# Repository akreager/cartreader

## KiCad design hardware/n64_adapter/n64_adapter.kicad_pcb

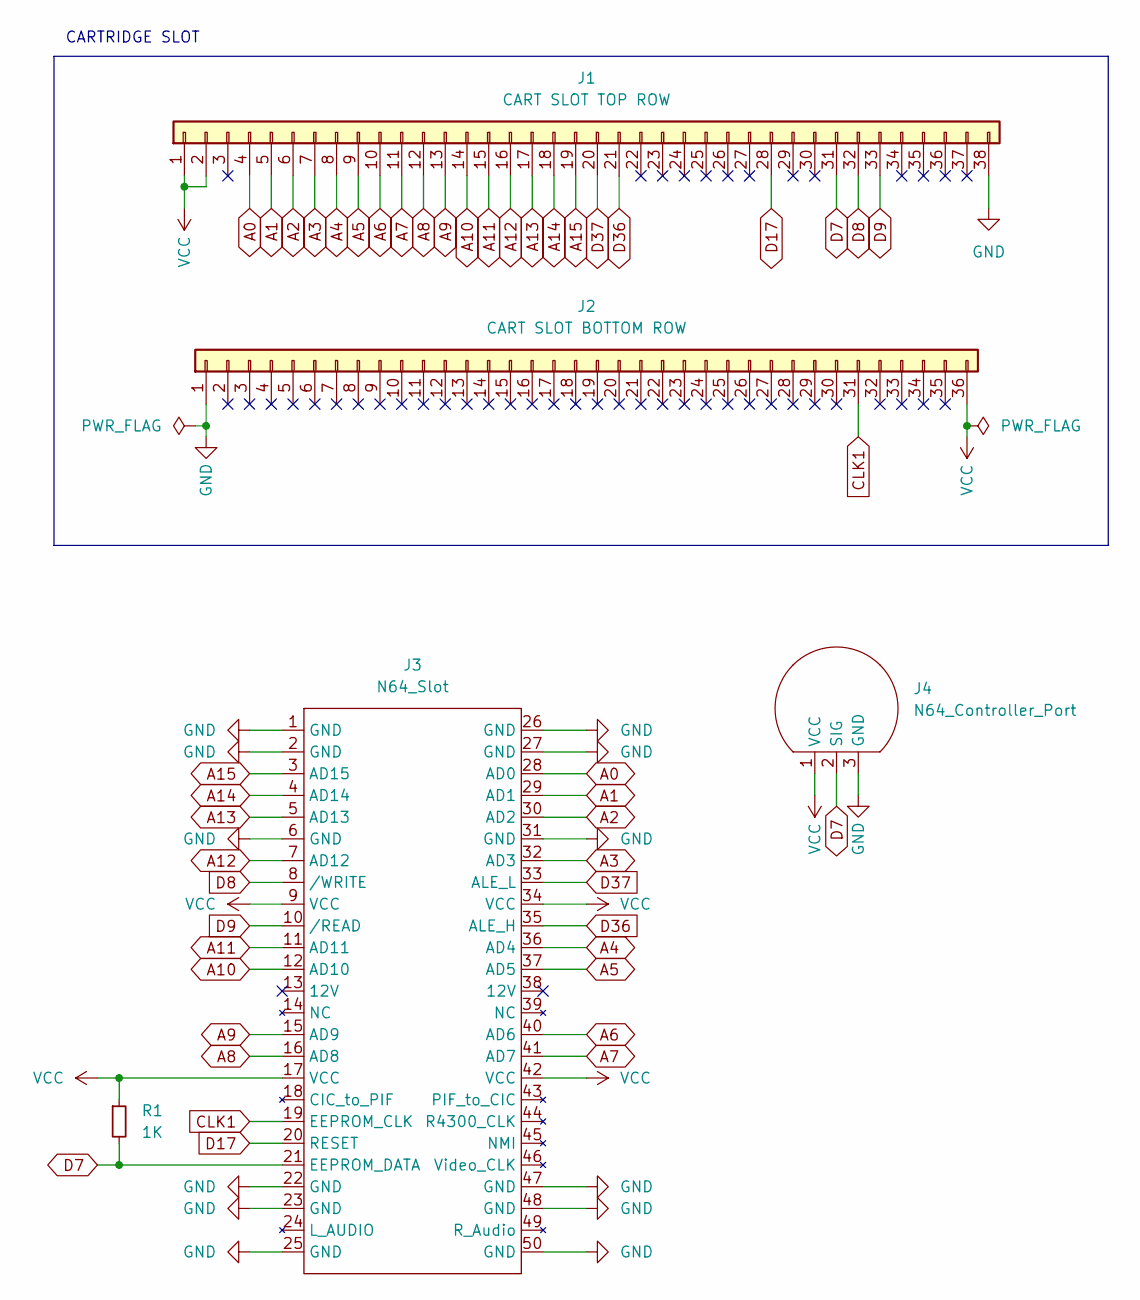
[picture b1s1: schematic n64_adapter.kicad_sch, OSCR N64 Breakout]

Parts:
J1: CART SLOT TOP ROW; PinHeader_1x38_P2.54mm_Vertical
J2: CART SLOT BOTTOM ROW; PinHeader_1x36_P2.54mm_Vertical
J3: N64_Slot; N64 Slot
J4: N64_Controller_Port; N64_CONTROLLER_PORT
R1: 1K; R_Axial_DIN0207_L6.3mm_D2.5mm_P10.16mm_Horizontal

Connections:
A0: J1.4, J3.28 (AD0)
A1: J1.5, J3.29 (AD1)
A2: J1.6, J3.30 (AD2)
A3: J1.7, J3.32 (AD3)
A4: J1.8, J3.36 (AD4)
A5: J1.9, J3.37 (AD5)
A6: J1.10, J3.40 (AD6)
A7: J1.11, J3.41 (AD7)
A8: J1.12, J3.16 (AD8)
A9: J1.13, J3.15 (AD9)
A10: J1.14, J3.12 (AD10)
A11: J1.15, J3.11 (AD11)
A12: J1.16, J3.7 (AD12)
A13: J1.17, J3.5 (AD13)
A14: J1.18, J3.4 (AD14)
A15: J1.19, J3.3 (AD15)
CLK1: J2.31, J3.19 (EEPROM_CLK)
D7: J1.31, J3.21 (EEPROM_DATA), J4.2 (SIG), R1.2
D8: J1.32, J3.8 (/WRITE)
D9: J1.33, J3.10 (/READ)
D17: J1.28, J3.20 (RESET)
D36: J1.21, J3.35 (ALE_H)
D37: J1.20, J3.33 (ALE_L)
GND: J1.38, J2.1, J3.1 (GND), J3.2 (GND), J3.6 (GND), J3.22 (GND), J3.23 (GND), J3.25 (GND), J3.26 (GND), J3.27 (GND), J3.31 (GND), J3.47 (GND), J3.48 (GND), J3.50 (GND), J4.3 (GND)
VCC: J1.1, J1.2, J2.36, J3.9 (VCC), J3.17 (VCC), J3.34 (VCC), J3.42 (VCC), J4.1 (VCC), R1.1

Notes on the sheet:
CARTRIDGE SLOT

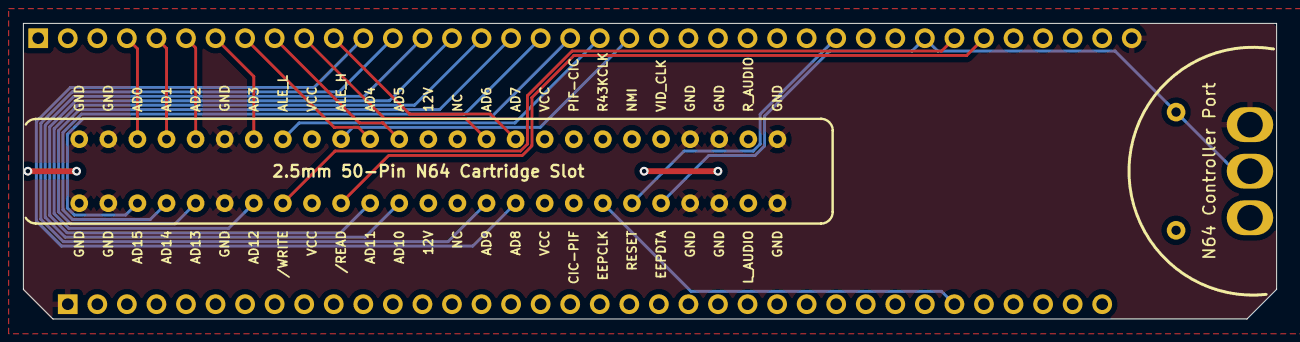
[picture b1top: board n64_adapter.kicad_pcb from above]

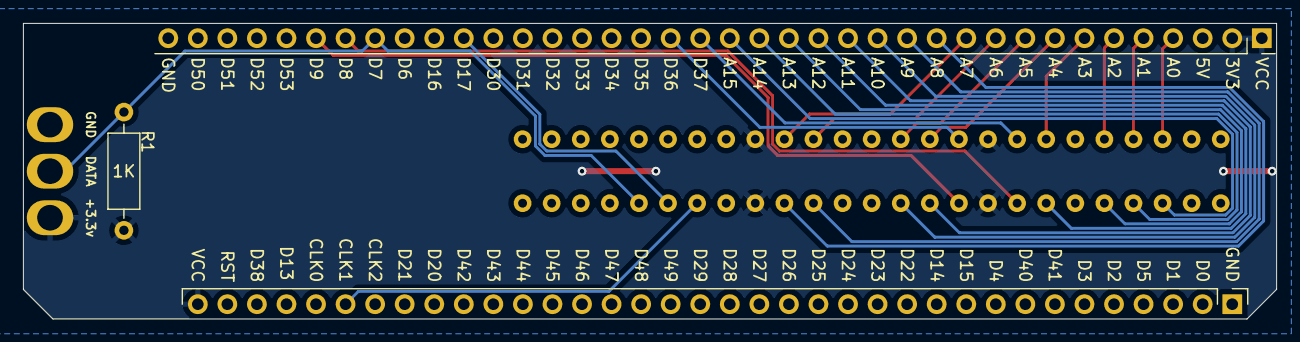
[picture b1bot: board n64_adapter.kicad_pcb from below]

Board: 2 copper layers, 107.7 x 25.4 mm, 5 parts (3 on the bottom side), 25 nets.

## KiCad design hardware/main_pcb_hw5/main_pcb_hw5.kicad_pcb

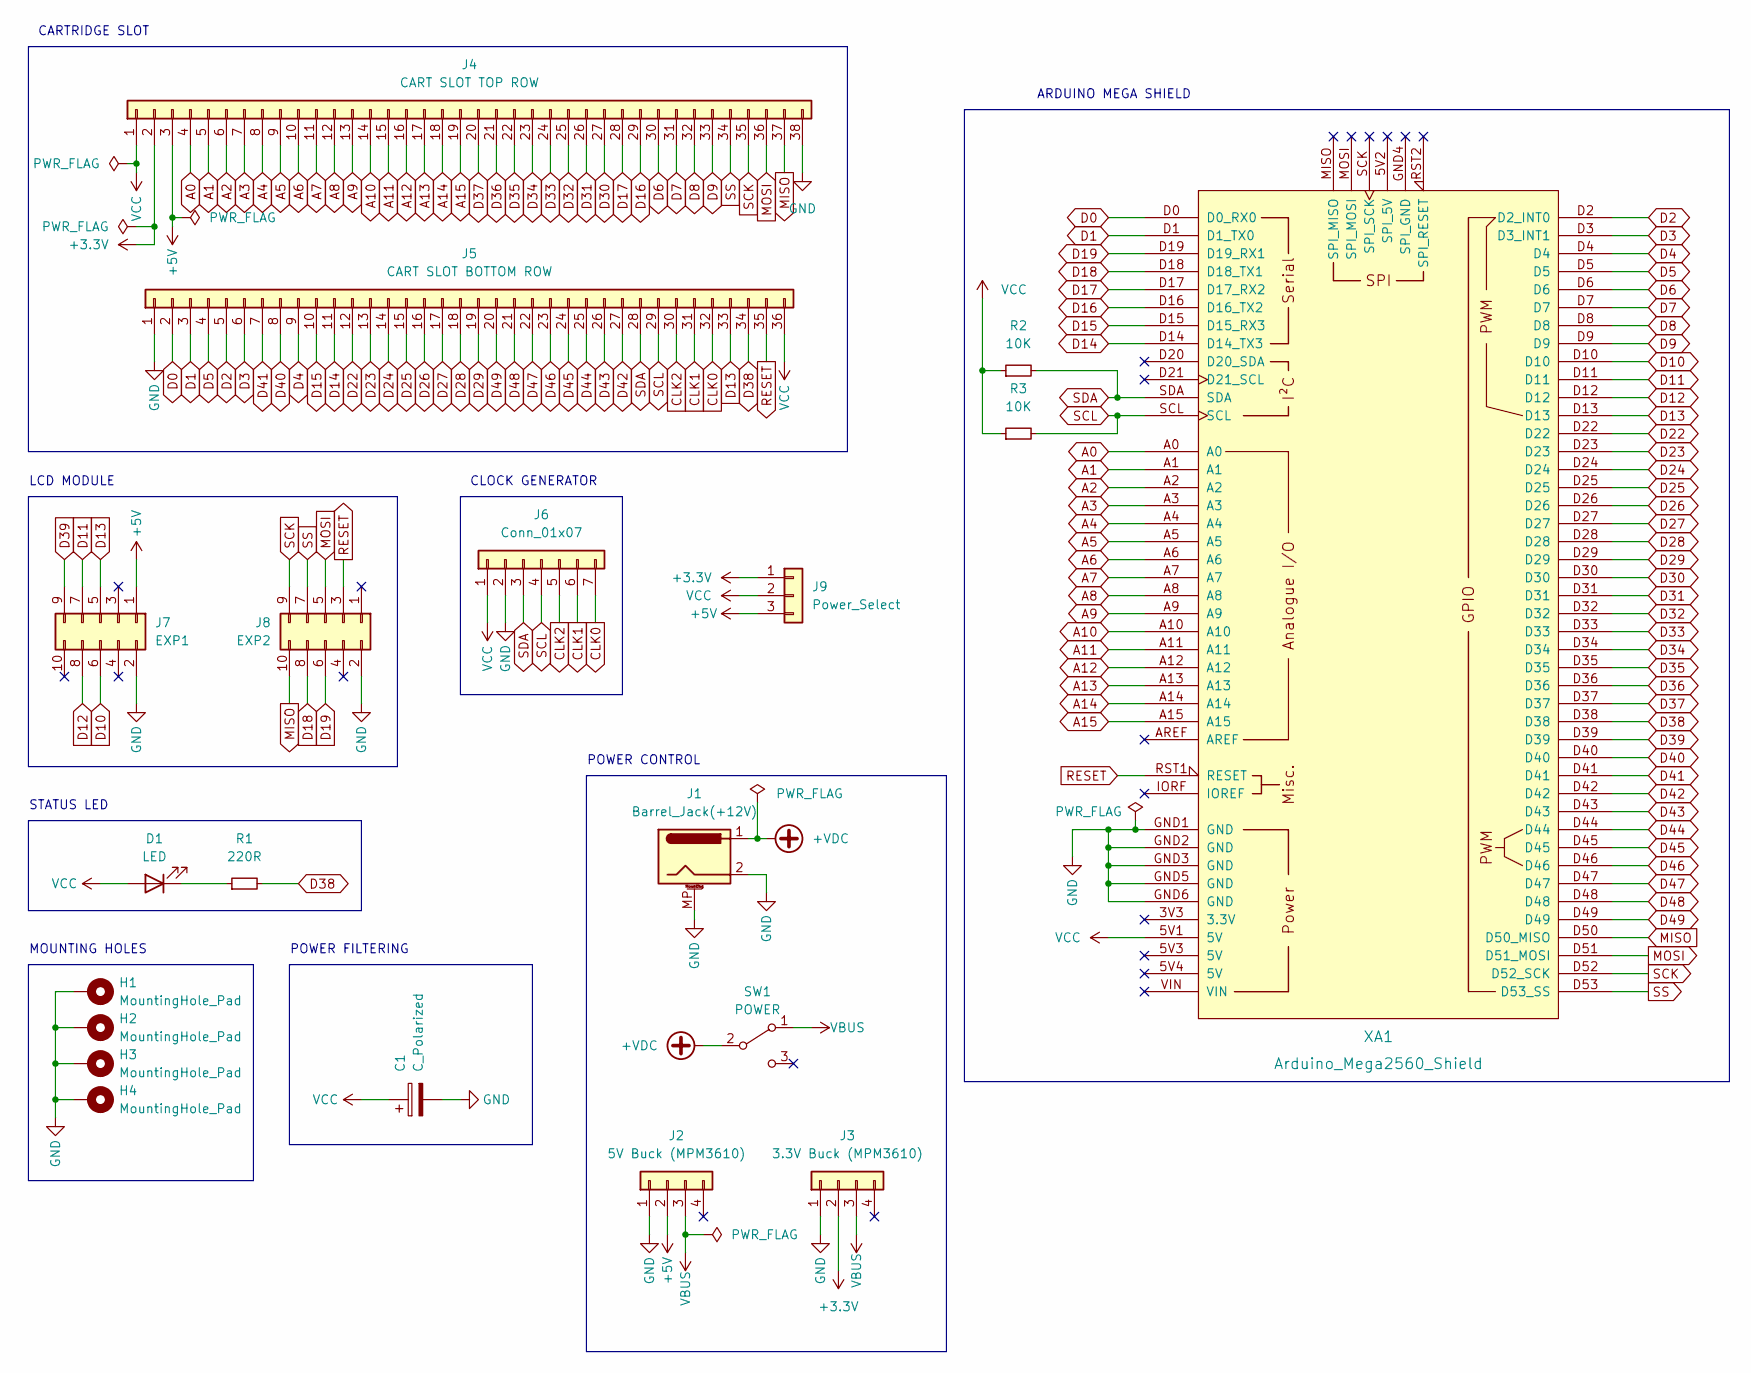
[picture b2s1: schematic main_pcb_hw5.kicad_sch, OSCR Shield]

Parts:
C1: C_Polarized; CP_Radial_D8.0mm_P3.50mm
D1: LED; LED_D3.0mm
H1, H2, H3, H4: MountingHole_Pad; MountingHole_3.2mm_M3_Pad
J1: Barrel_Jack(+12V); BarrelJack_Horizontal
J2: 5V Buck (MPM3610); PinHeader_1x04_P2.54mm_Vertical
J3: 3.3V Buck (MPM3610); PinHeader_1x04_P2.54mm_Vertical
J4: CART SLOT TOP ROW; PinSocket_1x38_P2.54mm_Vertical
J5: CART SLOT BOTTOM ROW; PinSocket_1x36_P2.54mm_Vertical
J6: Conn_01x07; PinSocket_1x07_P2.54mm_Vertical
J7: EXP1; IDC-Header_2x05_P2.54mm_Vertical
J8: EXP2; IDC-Header_2x05_P2.54mm_Vertical
J9: Power_Select; PinHeader_1x03_P2.54mm_Vertical
R1: 220R; R_Axial_DIN0207_L6.3mm_D2.5mm_P7.62mm_Horizontal
R2, R3: 10K; R_Axial_DIN0207_L6.3mm_D2.5mm_P7.62mm_Horizontal
SW1: POWER; SW_CuK_OS102011MA1QN1_SPDT_Angled
XA1: Arduino_Mega2560_Shield

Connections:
+3.3V: J3.2, J4.2, J9.1
+5V: J2.2, J4.3, J7.1, J9.3
+VDC: J1.1, SW1.2 (B)
A0: J4.4, XA1.A0
A1: J4.5, XA1.A1
A2: J4.6, XA1.A2
A3: J4.7, XA1.A3
A4: J4.8, XA1.A4
A5: J4.9, XA1.A5
A6: J4.10, XA1.A6
A7: J4.11, XA1.A7
A8: J4.12, XA1.A8
A9: J4.13, XA1.A9
A10: J4.14, XA1.A10
A11: J4.15, XA1.A11
A12: J4.16, XA1.A12
A13: J4.17, XA1.A13
A14: J4.18, XA1.A14
A15: J4.19, XA1.A15
CLK0: J5.32, J6.7
CLK1: J5.31, J6.6
CLK2: J5.30, J6.5
D0: J5.2, XA1.D0 (D0_RX0)
D1: J5.3, XA1.D1 (D1_TX0)
D2: J5.5, XA1.D2 (D2_INT0)
D3: J5.6, XA1.D3 (D3_INT1)
D4: J5.9, XA1.D4
D5: J5.4, XA1.D5
D6: J4.30, XA1.D6
D7: J4.31, XA1.D7
D8: J4.32, XA1.D8
D9: J4.33, XA1.D9
D10: J7.6, XA1.D10
D11: J7.7, XA1.D11
D12: J7.8, XA1.D12
D13: J5.33, J7.5, XA1.D13
D14: J5.11, XA1.D14 (D14_TX3)
D15: J5.10, XA1.D15 (D15_RX3)
D16: J4.29, XA1.D16 (D16_TX2)
D17: J4.28, XA1.D17 (D17_RX2)
D18: J8.8, XA1.D18 (D18_TX1)
D19: J8.6, XA1.D19 (D19_RX1)
D22: J5.12, XA1.D22
D23: J5.13, XA1.D23
D24: J5.14, XA1.D24
D25: J5.15, XA1.D25
D26: J5.16, XA1.D26
D27: J5.17, XA1.D27
D28: J5.18, XA1.D28
D29: J5.19, XA1.D29
D30: J4.27, XA1.D30
D31: J4.26, XA1.D31
D32: J4.25, XA1.D32
D33: J4.24, XA1.D33
D34: J4.23, XA1.D34
D35: J4.22, XA1.D35
D36: J4.21, XA1.D36
D37: J4.20, XA1.D37
D38: J5.34, R1.2, XA1.D38
D39: J7.9, XA1.D39
D40: J5.8, XA1.D40
D41: J5.7, XA1.D41
D42: J5.27, XA1.D42
D43: J5.26, XA1.D43
D44: J5.25, XA1.D44
D45: J5.24, XA1.D45
D46: J5.23, XA1.D46
D47: J5.22, XA1.D47
D48: J5.21, XA1.D48
D49: J5.20, XA1.D49
GND: C1.2, H1.1, H2.1, H3.1, H4.1, J1.2, J1.MP (MountPin), J2.1, J3.1, J4.38, J5.1, J6.2, J7.2, J8.2, XA1.GND1 (GND), XA1.GND2 (GND), XA1.GND3 (GND), XA1.GND5 (GND), XA1.GND6 (GND)
MISO: J4.37, J8.10, XA1.D50 (D50_MISO)
MOSI: J4.36, J8.5, XA1.D51 (D51_MOSI)
unnamed: D1.1 (K), R1.1
RESET: J5.35, J8.3, XA1.RST1 (RESET)
SCK: J4.35, J8.9, XA1.D52 (D52_SCK)
SCL: J5.29, J6.4, R3.2, XA1.SCL
SDA: J5.28, J6.3, R2.2, XA1.SDA
SS: J4.34, J8.7, XA1.D53 (D53_SS)
VBUS: J2.3, J3.3, SW1.1 (A)
VCC: C1.1, D1.2 (A), J4.1, J5.36, J6.1, J9.2, R2.1, R3.1, XA1.5V1 (5V)

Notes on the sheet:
STATUS LED
POWER CONTROL
LCD MODULE
CLOCK GENERATOR
CARTRIDGE SLOT
POWER FILTERING
ARDUINO MEGA SHIELD
MOUNTING HOLES

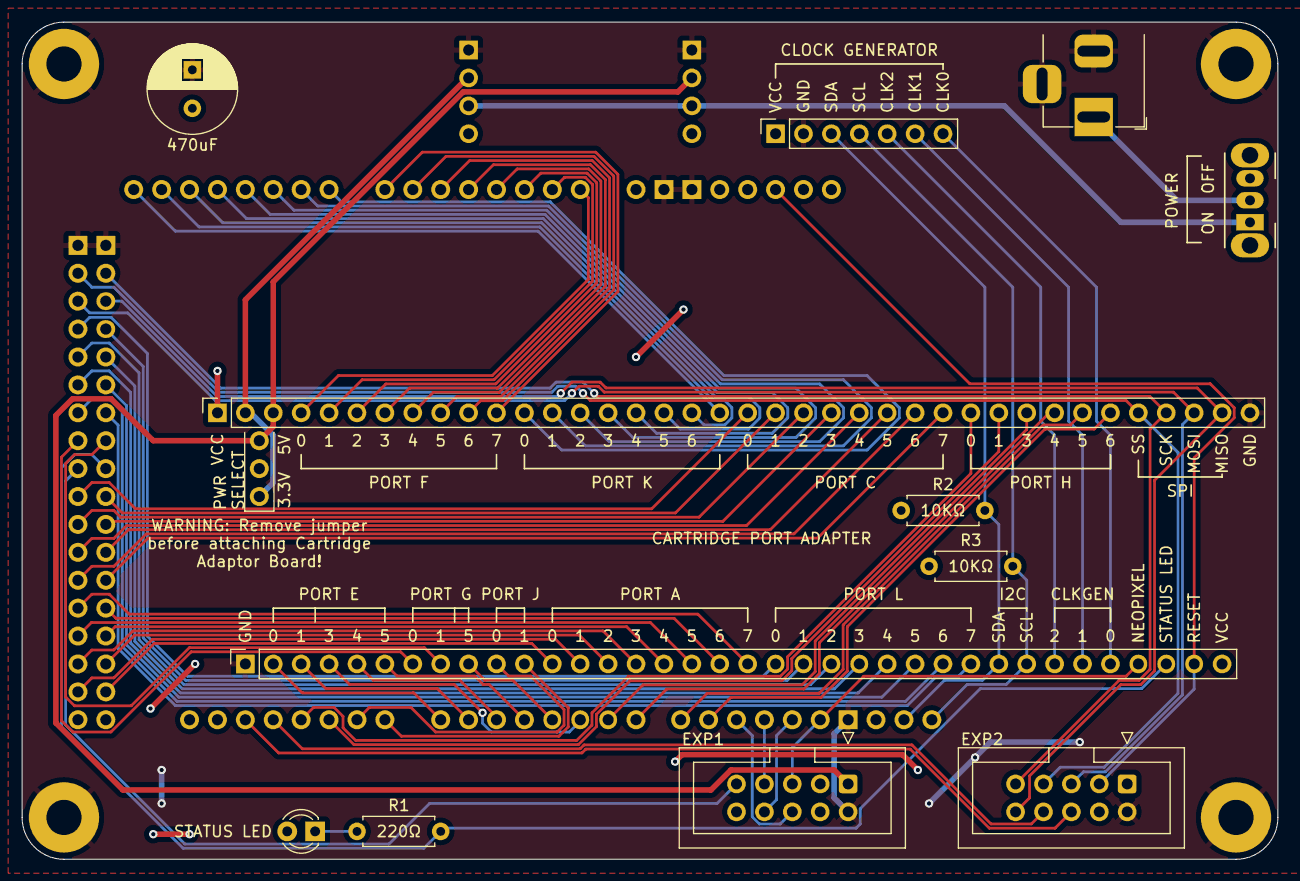
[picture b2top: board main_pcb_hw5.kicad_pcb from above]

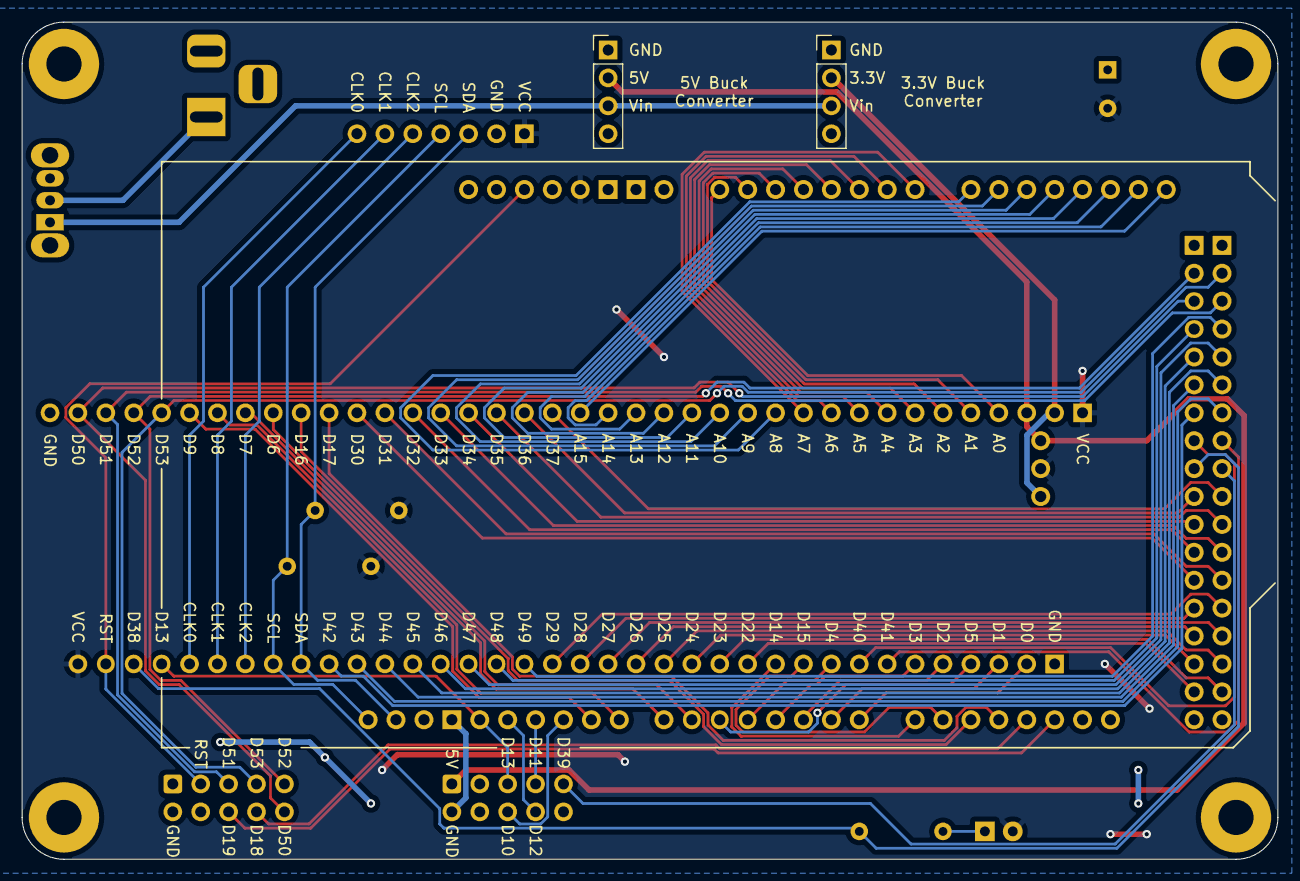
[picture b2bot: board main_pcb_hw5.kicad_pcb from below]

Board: 2 copper layers, 114.3 x 76.2 mm, 20 parts (2 on the bottom side), 81 nets.

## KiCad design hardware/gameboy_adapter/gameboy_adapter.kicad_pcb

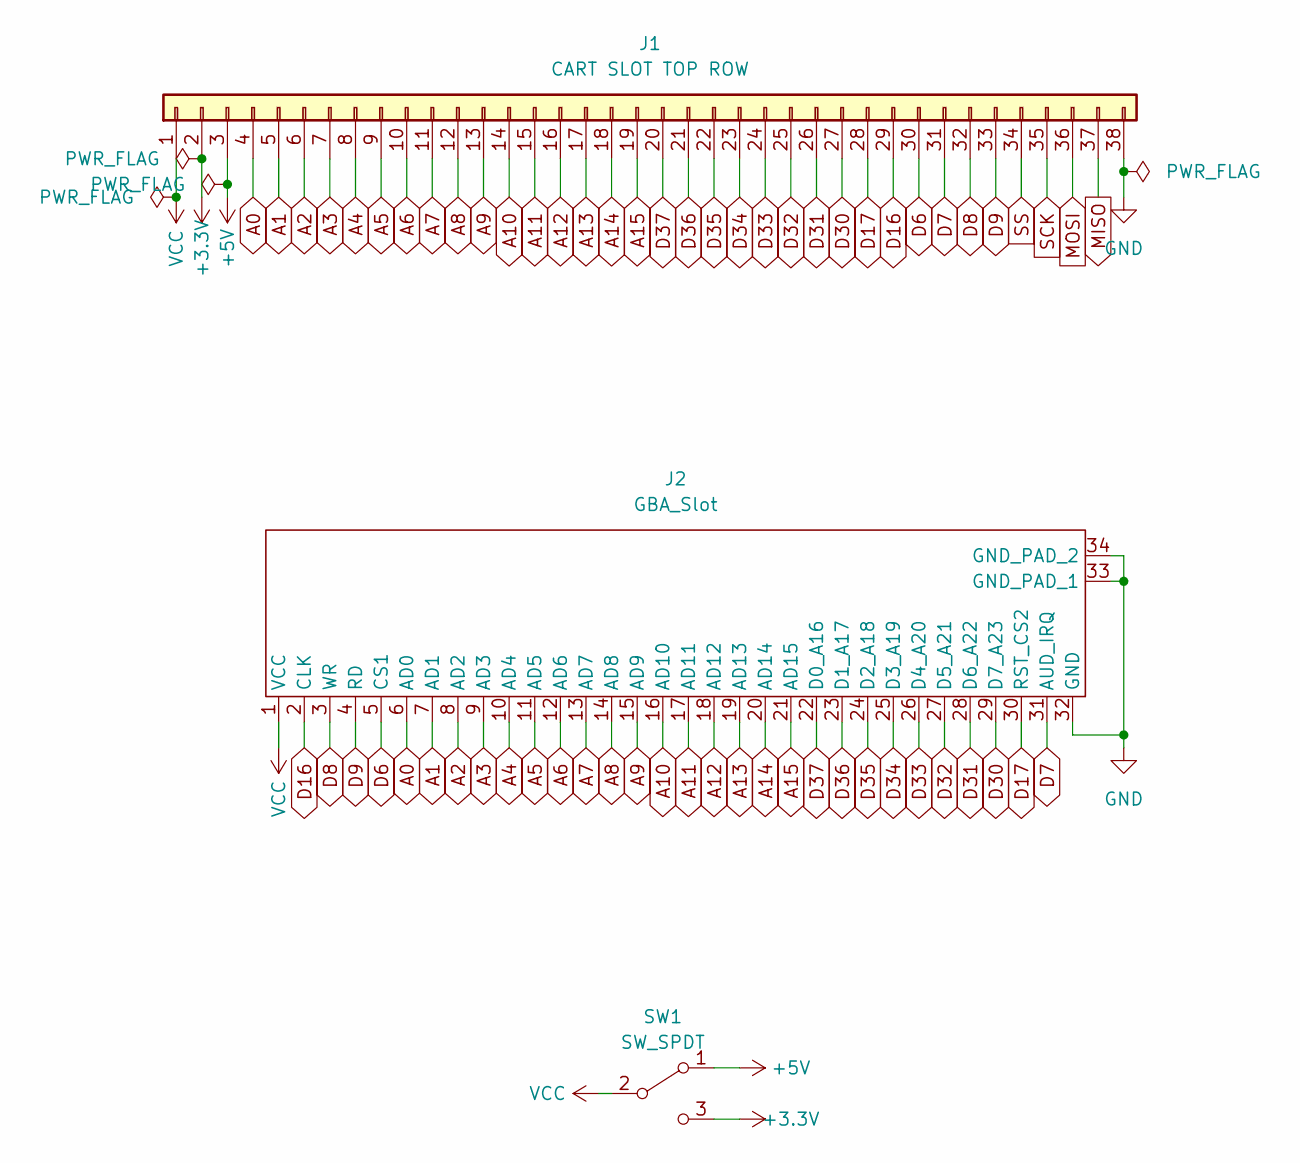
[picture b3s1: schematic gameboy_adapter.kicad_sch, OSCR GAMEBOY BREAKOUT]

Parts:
J1: CART SLOT TOP ROW; PinHeader_1x38_P2.54mm_Vertical
J2: GBA_Slot
SW1: SW_SPDT; SW_CuK_OS102011MA1QN1_SPDT_Angled

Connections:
+3.3V: J1.2, SW1.3 (C)
+5V: J1.3, SW1.1 (A)
A0: J1.4, J2.6 (AD0)
A1: J1.5, J2.7 (AD1)
A2: J1.6, J2.8 (AD2)
A3: J1.7, J2.9 (AD3)
A4: J1.8, J2.10 (AD4)
A5: J1.9, J2.11 (AD5)
A6: J1.10, J2.12 (AD6)
A7: J1.11, J2.13 (AD7)
A8: J1.12, J2.14 (AD8)
A9: J1.13, J2.15 (AD9)
A10: J1.14, J2.16 (AD10)
A11: J1.15, J2.17 (AD11)
A12: J1.16, J2.18 (AD12)
A13: J1.17, J2.19 (AD13)
A14: J1.18, J2.20 (AD14)
A15: J1.19, J2.21 (AD15)
D6: J1.30, J2.5 (CS1)
D7: J1.31, J2.31 (AUD_IRQ)
D8: J1.32, J2.3 (WR)
D9: J1.33, J2.4 (RD)
D16: J1.29, J2.2 (CLK)
D17: J1.28, J2.30 (RST_CS2)
D30: J1.27, J2.29 (D7_A23)
D31: J1.26, J2.28 (D6_A22)
D32: J1.25, J2.27 (D5_A21)
D33: J1.24, J2.26 (D4_A20)
D34: J1.23, J2.25 (D3_A19)
D35: J1.22, J2.24 (D2_A18)
D36: J1.21, J2.23 (D1_A17)
D37: J1.20, J2.22 (D0_A16)
GND: J1.38, J2.32 (GND), J2.33 (GND_PAD_1), J2.34 (GND_PAD_2)
MISO: J1.37
MOSI: J1.36
SCK: J1.35
SS: J1.34
VCC: J1.1, J2.1 (VCC), SW1.2 (B)

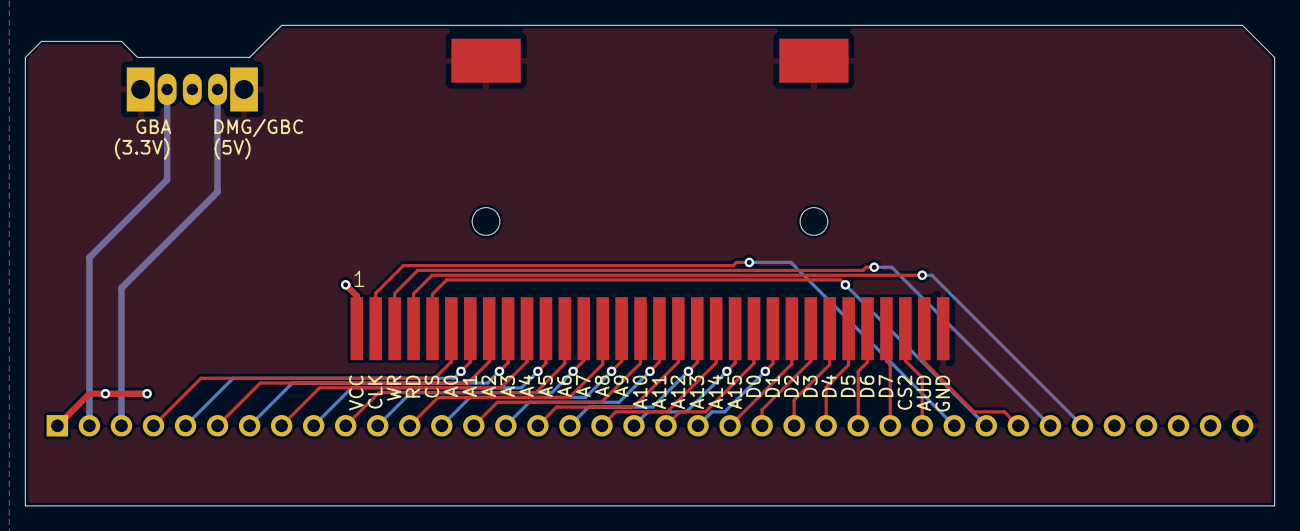
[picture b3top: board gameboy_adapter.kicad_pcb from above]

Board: 2 copper layers, 99.1 x 38.1 mm, 3 parts (1 on the bottom side), 34 nets.

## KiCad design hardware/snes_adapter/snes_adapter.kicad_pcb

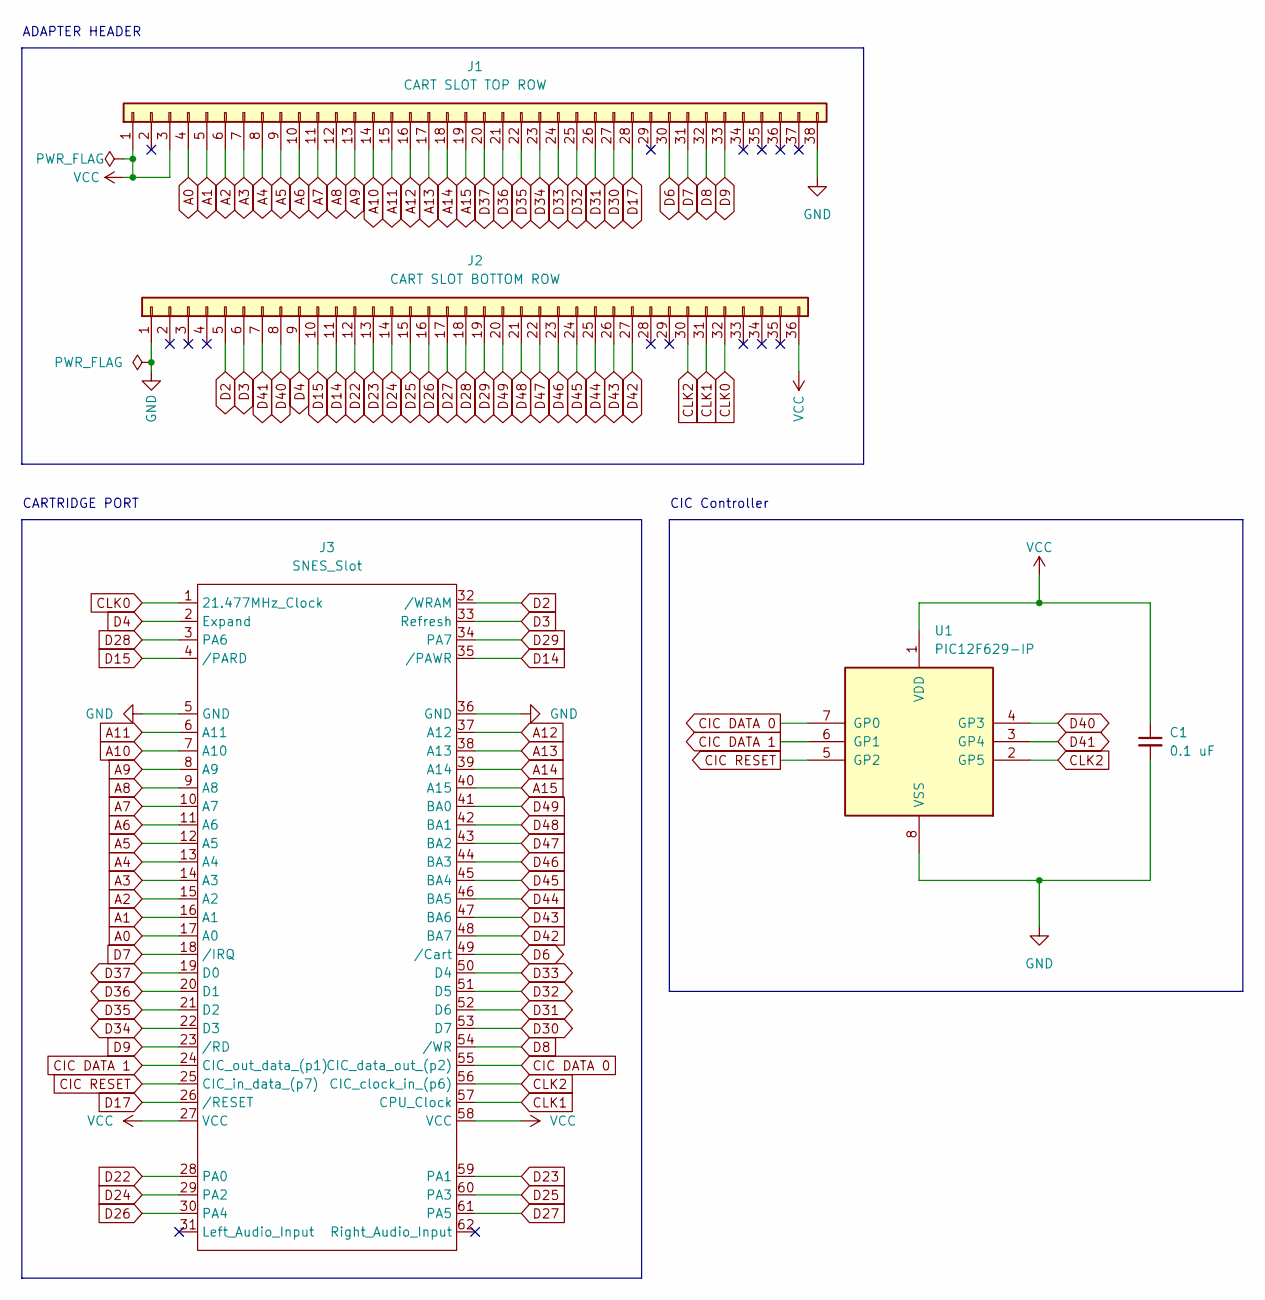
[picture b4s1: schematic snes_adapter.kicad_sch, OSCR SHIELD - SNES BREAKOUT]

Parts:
C1: 0.1 uF; C_Disc_D5.0mm_W2.5mm_P5.00mm
J1: CART SLOT TOP ROW; PinHeader_1x38_P2.54mm_Vertical
J2: CART SLOT BOTTOM ROW; PinHeader_1x36_P2.54mm_Vertical
J3: SNES_Slot; SNES Slot
U1: PIC12F629-IP; DIP-8_W7.62mm

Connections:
A0: J1.4, J3.17 (A0)
A1: J1.5, J3.16 (A1)
A2: J1.6, J3.15 (A2)
A3: J1.7, J3.14 (A3)
A4: J1.8, J3.13 (A4)
A5: J1.9, J3.12 (A5)
A6: J1.10, J3.11 (A6)
A7: J1.11, J3.10 (A7)
A8: J1.12, J3.9 (A8)
A9: J1.13, J3.8 (A9)
A10: J1.14, J3.7 (A10)
A11: J1.15, J3.6 (A11)
A12: J1.16, J3.37 (A12)
A13: J1.17, J3.38 (A13)
A14: J1.18, J3.39 (A14)
A15: J1.19, J3.40 (A15)
CIC DATA 0: J3.55 (CIC_data_out_(p2)), U1.7 (GP0)
CIC DATA 1: J3.24 (CIC_out_data_(p1)), U1.6 (GP1)
CIC RESET: J3.25 (CIC_in_data_(p7)), U1.5 (GP2)
CLK0: J2.32, J3.1 (21.477MHz_Clock)
CLK1: J2.31, J3.57 (CPU_Clock)
CLK2: J2.30, J3.56 (CIC_clock_in_(p6)), U1.2 (GP5)
D2: J2.5, J3.32 (/WRAM)
D3: J2.6, J3.33 (Refresh)
D4: J2.9, J3.2 (Expand)
D6: J1.30, J3.49 (/Cart)
D7: J1.31, J3.18 (/IRQ)
D8: J1.32, J3.54 (/WR)
D9: J1.33, J3.23 (/RD)
D14: J2.11, J3.35 (/PAWR)
D15: J2.10, J3.4 (/PARD)
D17: J1.28, J3.26 (/RESET)
D22: J2.12, J3.28 (PA0)
D23: J2.13, J3.59 (PA1)
D24: J2.14, J3.29 (PA2)
D25: J2.15, J3.60 (PA3)
D26: J2.16, J3.30 (PA4)
D27: J2.17, J3.61 (PA5)
D28: J2.18, J3.3 (PA6)
D29: J2.19, J3.34 (PA7)
D30: J1.27, J3.53 (D7)
D31: J1.26, J3.52 (D6)
D32: J1.25, J3.51 (D5)
D33: J1.24, J3.50 (D4)
D34: J1.23, J3.22 (D3)
D35: J1.22, J3.21 (D2)
D36: J1.21, J3.20 (D1)
D37: J1.20, J3.19 (D0)
D40: J2.8, U1.4 (GP3)
D41: J2.7, U1.3 (GP4)
D42: J2.27, J3.48 (BA7)
D43: J2.26, J3.47 (BA6)
D44: J2.25, J3.46 (BA5)
D45: J2.24, J3.45 (BA4)
D46: J2.23, J3.44 (BA3)
D47: J2.22, J3.43 (BA2)
D48: J2.21, J3.42 (BA1)
D49: J2.20, J3.41 (BA0)
GND: C1.2, J1.38, J2.1, J3.5 (GND), J3.36 (GND), U1.8 (VSS)
VCC: C1.1, J1.1, J1.3, J2.36, J3.27 (VCC), J3.58 (VCC), U1.1 (VDD)

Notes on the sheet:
CARTRIDGE PORT
ADAPTER HEADER
CIC Controller

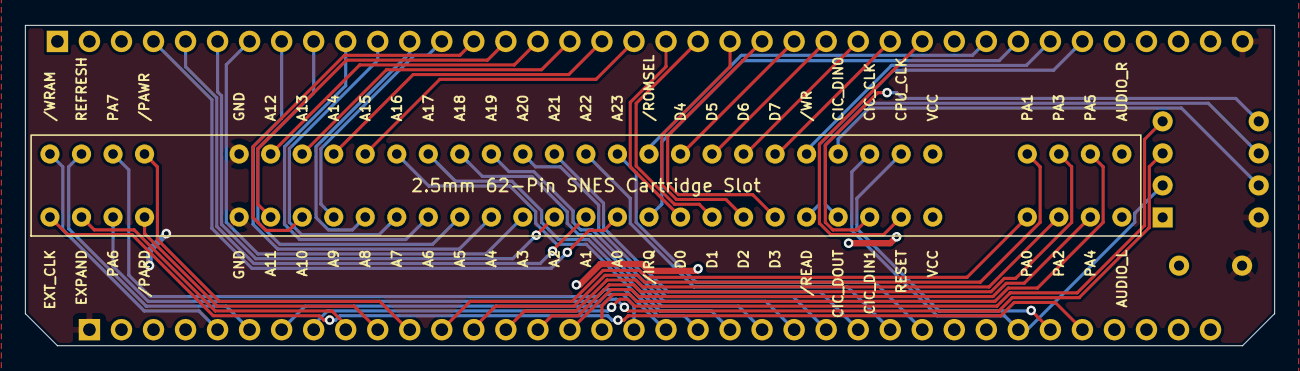
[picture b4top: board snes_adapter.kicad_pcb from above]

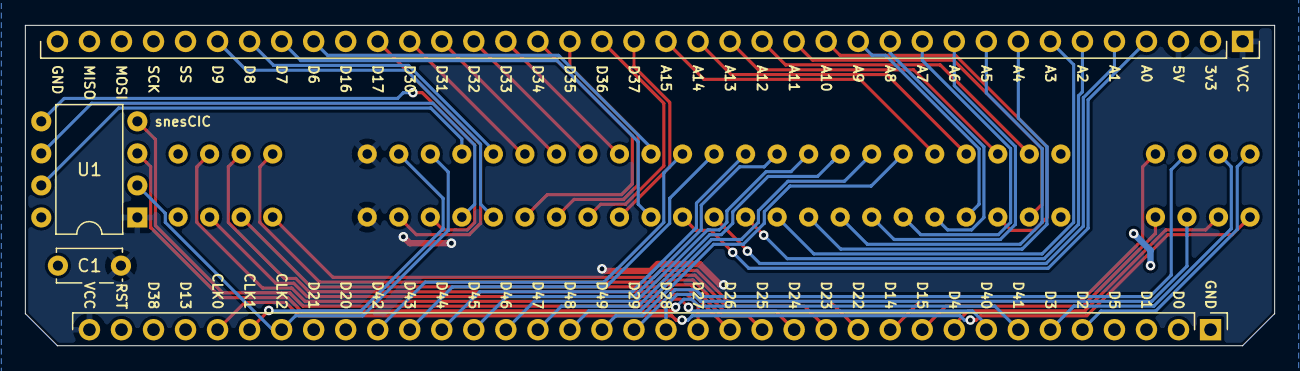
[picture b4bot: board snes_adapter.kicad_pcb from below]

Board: 2 copper layers, 99.1 x 25.4 mm, 5 parts (4 on the bottom side), 60 nets.

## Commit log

2023-01-22 relink footprints to symbols
2023-01-22 remove gba slot from main pcb
    GBA cart slot is removed to simplify and shrink the main PCB.
2023-01-22 Add some RepRap hardware reference documents
2023-01-23 Add RepRap discount LCD Schematics
2023-01-23 add gitignore file do block backup archives
2023-01-23 move gitignore to root
2023-01-23 Change MCU module on schematic
    Replace Mega embed with standard Mega R3.
    Added 2 voltage regulators to main pcb.
    -moved voltage selection to daughterboard (remove main switch)
2023-01-24 export schematic pdf
2023-01-24 update n64 breakout
    Propagate changes from main PCB to N64 breakout board
2023-01-24 update schematic
    propagate changes from main PCB to GB breakout
2023-01-24 export gba schematic to pdf
2023-01-24 export n64 schematic to pdf
2023-01-24 update snes breakout
    propagate changes in main pcb to snes breakout
2023-01-30 Move .gitignore to main branch
2023-02-07 wip; down sizing and re-routing traces
2023-02-07 add screenshots of cic adaptor in preparation to move cic micro to adaptor
2023-02-07 Squashed commit of the following:
    commit 43cf43e73f575c07617f32c35a9656c33d9a403a
    Merge: a5cbf6d 016ed2d
    Author: Allen Kreager <akreager87@gmail.com>
    Date: Tue Feb 7 11:51:59 2023 -0500
    Merge remote-tracking branch 'upstream/master'
    commit 016ed2ded5fc8d7fdf859fa5899efe3ff06786a0
2023-02-09 Update SNES slot footprint
    Add top silkscreen of pinout and outline of the slot. Outline dimensions have not been verified.
2023-02-09 Squashed commit of the following:
    commit 37b85b88ed66b614c05e25f253aeb0bac34508a8
    Author: Allen Kreager <akreager87@gmail.com>
    Date: Thu Feb 9 10:53:52 2023 -0500
    Update SNES slot footprint
    Add top silkscreen of pinout and outline of the slot. Outline dimensions have not been verified.
    commit 43cf43e73f575c07617f32c35a9656c33d9a403a
2023-02-10 Move cic uc to SNES breakout board and update
2023-02-10 Squashed commit of the following:
    commit 3d58a743cb495f545c0d759f5cf4dcd5fc7c203e
    Merge: 43cf43e 6959c05
    Author: Allen Kreager <akreager87@gmail.com>
    Date: Fri Feb 10 09:45:36 2023 -0500
    Merge remote-tracking branch 'upstream/master'
    commit 6959c055e62be0797ab2662c92fea933da4fcc29
2023-02-10 Move SNES updates to clean branch
2023-02-10 Move main PCB updates to clean branch
2023-02-10 update schematic
    relink GBA symbol; rename SPI pins on main header; relink footprints
2023-02-10 change footprint of cart slot to pin header
2023-02-10 add ground pads to GBA schematic and update footprint
2023-02-10 Update gb breakout
2023-02-12 Create N64 Controller port symbol and footprint.
2023-02-12 Update N64 breakout
    add controller port to schematic and board. change board to inch standard, minimize trace width and reroute all traces. realign bottom silkscreen to pins.
2023-02-16 Update Main PCB
    Change basic design to a shield. Remove GBA Port. Add buck converters to main board.
2023-02-28 Update N64 controller port footprint
    Adjust silkscreen and add 3D model.
2023-02-28 Adjust silkscreen for N64 slot
2023-02-28 Update N64 cart slot footprint
    *!ADJUST PIN SPACING TO MATCH MEASURED PART!*
    Adjust silkscreen and add 3D model.
2023-03-02 update SNES ports
    Add type A and type B port.
2023-03-02 Update SNES Slot, Type A.kicad_mod
    Add 3D model
2023-03-02 move step files to footprints folder
    End users may need to relink the step files on their system.
2023-03-02 Update N64_CONTROLLER_PORT.kicad_mod
    add courtyard
2023-03-02 Update N64 Slot.kicad_mod
    Add courtyard.
2023-03-05 finalize n64 breakout design
    Ready for RTM
2023-03-06 update GBA Slot
    Add 3D model
